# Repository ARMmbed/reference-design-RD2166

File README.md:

# RD2166 Introduction:

The RD2166 Reference Design is a Pelion Ready design based on the Quectel BG96 cellular module and the STM32L475 Microcontroller.

The reference design is a tested and proven starting point targetted towards the creation of both Development Boards and End Products.

# Reference Design Contents:
**Reference Schematic** 
This is the core of reference design, and illustrates where and how the essential components are connected. 

**Reference Application**
Built on mbedOS, and includes Pelion Device Manager. This application has been configured to run on the Reference Design hardware, and will connect to the Pelion Cloud, and is capable of running the cloud based update service.
Please refer to the [\Documentation\RD2166_Readme.md](https://github.com/ARMmbed/reference-design-RD2166/blob/master/Documentation/RD2166_README.md) for instructions on how to build & use this example application.

**Example Implementation** 
Based on the Reference Design, this example implementation is included to demonstrate the Reference Design being used to create real-world hardware. The example implemenation is used within Arm to include the Reference Design into the internal test infrastructure, it is comprised of three parts:

*MCB (Module Carrier Board)* - this has been designed using the Reference Design schematic. In this reference design, the MCB is a standalone STM32L475 MCU.

*MEB (Module Expansion Board)* - this has been designed using the Reference Design schematic. In this reference design, the MEB is a Quectel BG96 module.

*MTB (Module Test Bed)* - this is part of the test infrastructure, and includes DAPLink circuit for programming the device, a range of I/O and loopback paths for automated testing.

# Version Information:
		
| Release | mbed OS | mbed Cloud Client | Release Date | Comment |
| --- | --- | --- | --- | --- | 
|v1.0 | 5.11.5	| 2.0.1.1	| 27/02/2019 | Initial Release
| |  |  |   | 

Back to [Reference Designs](https://github.com/ARMmbed/reference-designs)

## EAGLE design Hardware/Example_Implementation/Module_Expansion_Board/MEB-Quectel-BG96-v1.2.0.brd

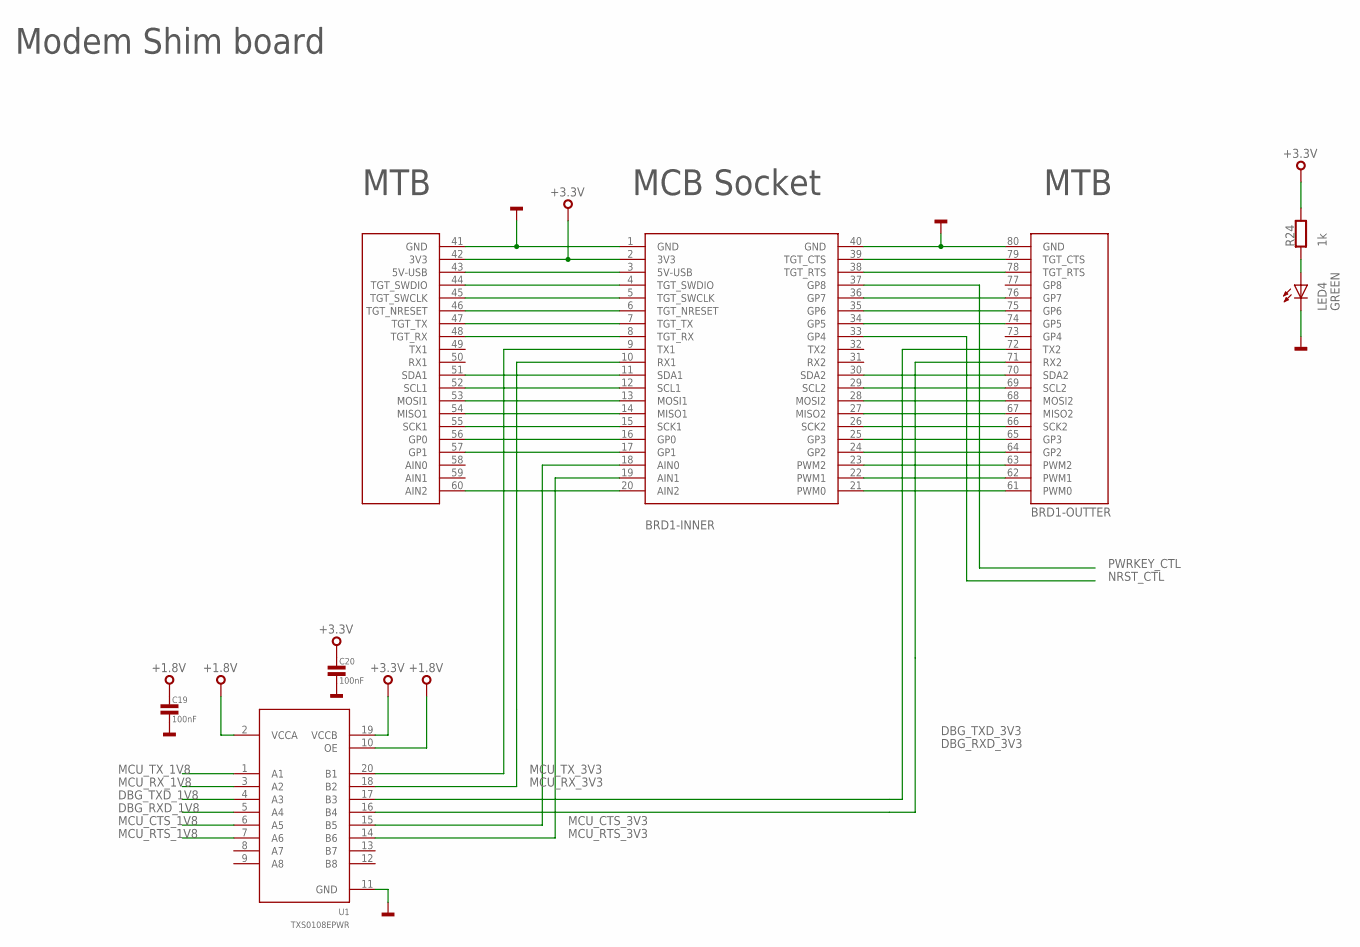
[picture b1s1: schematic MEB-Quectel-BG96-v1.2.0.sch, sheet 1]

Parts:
BRD1: MODULE-SHIM; MODULE_SOCKET
C19, C20: 100nF; 0603
LED4: GREEN; CHIPLED_0603
R24: 1k; 0603
U1: TXS0108EPWR; TSSOP-20

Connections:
+1.8V: C19.1, U1.2 (VCCA), U1.10 (OE); also elsewhere on the board
+3.3V: BRD1.2 (3V3), BRD1.42 (3V3), C20.1, R24.2, U1.19 (VCCB)
DBG_RXD_1V8: U1.5 (A4); also elsewhere on the board
DBG_RXD_3V3: BRD1.71 (RX2), U1.16 (B4)
DBG_TXD_1V8: U1.4 (A3); also elsewhere on the board
DBG_TXD_3V3: BRD1.72 (TX2), U1.17 (B3)
GND: BRD1.1 (GND), BRD1.40 (GND), BRD1.41 (GND), BRD1.80 (GND), C19.2, C20.2, LED4.C, U1.11 (GND); also elsewhere on the board
MCU_CTS_1V8: U1.6 (A5); also elsewhere on the board
MCU_CTS_3V3: BRD1.18 (AIN0), U1.15 (B5)
MCU_RTS_1V8: U1.7 (A6); also elsewhere on the board
MCU_RTS_3V3: BRD1.19 (AIN1), U1.14 (B6)
MCU_RX_1V8: U1.3 (A2); also elsewhere on the board
MCU_RX_3V3: BRD1.10 (RX1), U1.18 (B2)
MCU_TX_1V8: U1.1 (A1); also elsewhere on the board
MCU_TX_3V3: BRD1.9 (TX1), U1.20 (B1)
unnamed: LED4.A, R24.1
unnamed: BRD1.39 (TGT_CTS), BRD1.79 (TGT_CTS)
unnamed: BRD1.38 (TGT_RTS), BRD1.78 (TGT_RTS)
unnamed: BRD1.36 (GP7), BRD1.76 (GP7)
unnamed: BRD1.35 (GP6), BRD1.75 (GP6)
unnamed: BRD1.34 (GP5), BRD1.74 (GP5)
unnamed: BRD1.30 (SDA2), BRD1.70 (SDA2)
unnamed: BRD1.29 (SCL2), BRD1.69 (SCL2)
unnamed: BRD1.28 (MOSI2), BRD1.68 (MOSI2)
unnamed: BRD1.27 (MISO2), BRD1.67 (MISO2)
unnamed: BRD1.26 (SCK2), BRD1.66 (SCK2)
unnamed: BRD1.25 (GP3), BRD1.65 (GP3)
unnamed: BRD1.24 (GP2), BRD1.64 (GP2)
unnamed: BRD1.23 (PWM2), BRD1.63 (PWM2)
unnamed: BRD1.22 (PWM1), BRD1.62 (PWM1)
unnamed: BRD1.21 (PWM0), BRD1.61 (PWM0)
unnamed: BRD1.3 (5V-USB), BRD1.43 (5V-USB)
unnamed: BRD1.4 (TGT_SWDIO), BRD1.44 (TGT_SWDIO)
unnamed: BRD1.5 (TGT_SWCLK), BRD1.45 (TGT_SWCLK)
unnamed: BRD1.6 (TGT_NRESET), BRD1.46 (TGT_NRESET)
unnamed: BRD1.7 (TGT_TX), BRD1.47 (TGT_TX)
unnamed: BRD1.8 (TGT_RX), BRD1.48 (TGT_RX)
unnamed: BRD1.11 (SDA1), BRD1.51 (SDA1)
unnamed: BRD1.12 (SCL1), BRD1.52 (SCL1)
unnamed: BRD1.13 (MOSI1), BRD1.53 (MOSI1)
unnamed: BRD1.14 (MISO1), BRD1.54 (MISO1)
unnamed: BRD1.15 (SCK1), BRD1.55 (SCK1)
unnamed: BRD1.16 (GP0), BRD1.56 (GP0)
unnamed: BRD1.17 (GP1), BRD1.57 (GP1)
unnamed: BRD1.20 (AIN2), BRD1.60 (AIN2)
NRST_CTL: BRD1.33 (GP4); also elsewhere on the board
PWRKEY_CTL: BRD1.37 (GP8); also elsewhere on the board

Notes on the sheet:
Modem Shim board
MCB Socket
MTB

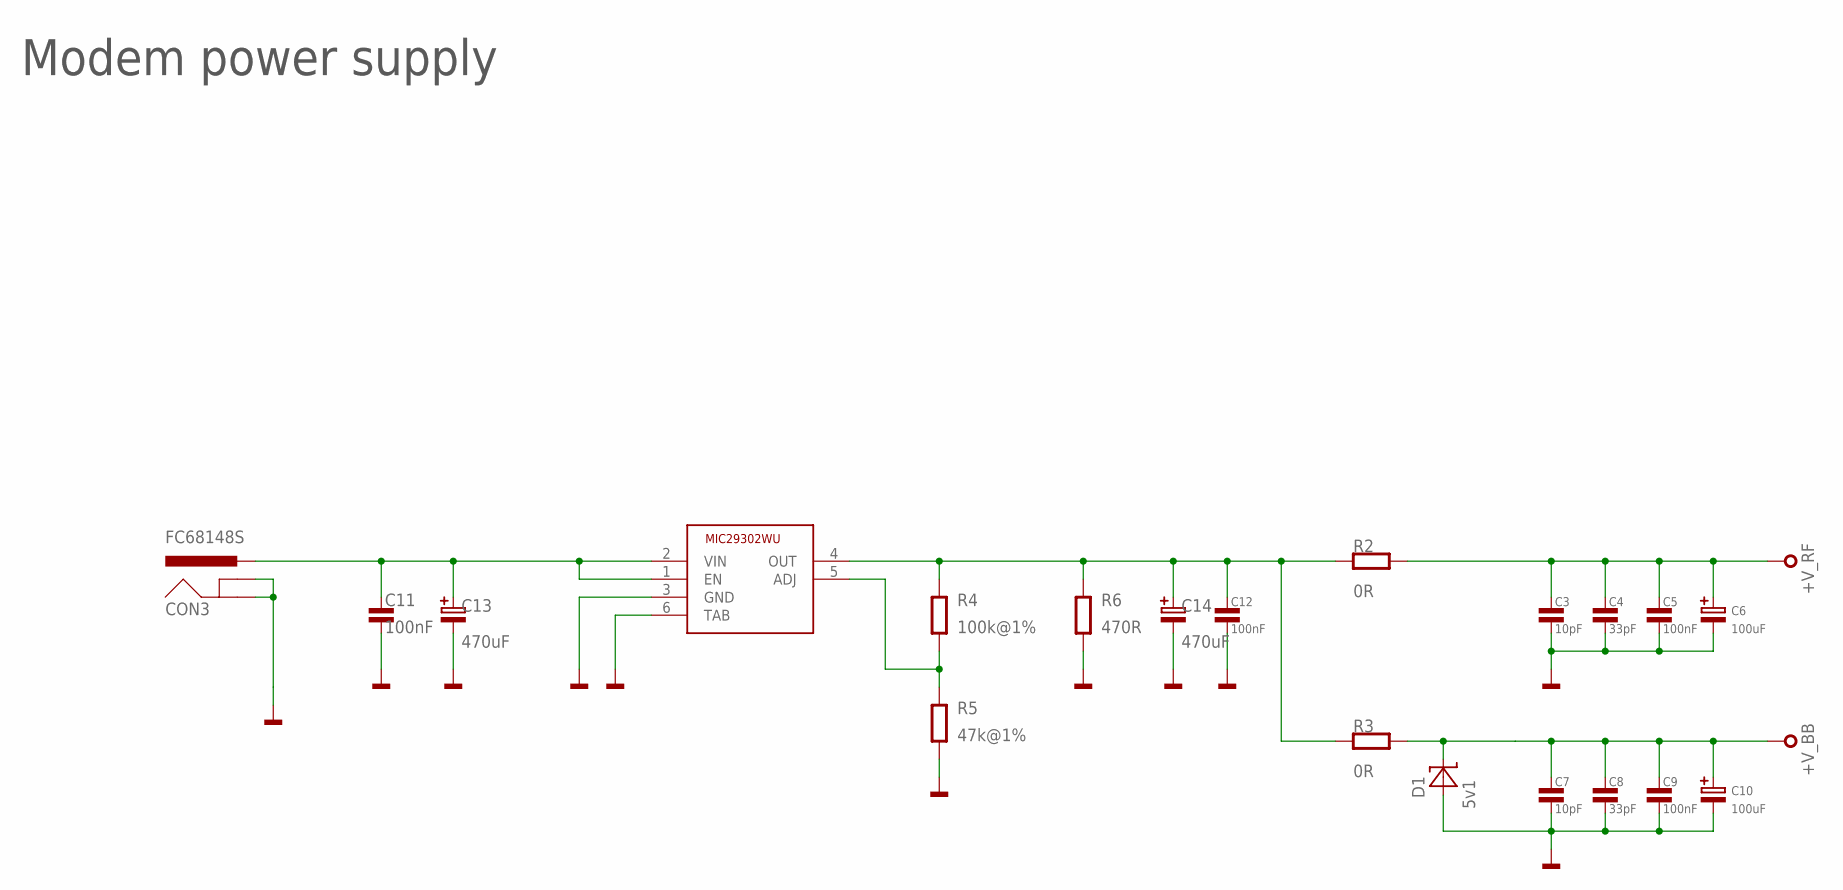
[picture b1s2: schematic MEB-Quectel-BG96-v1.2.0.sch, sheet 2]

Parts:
C3, C7: 10pF; 0603
C4, C8: 33pF; 0603
C5, C9, C11, C12: 100nF; 0603
C6, C10: 100uF; SMC_A
C13, C14: 470uF; PANASONIC_F
CON3: FC68148S
D1: 5v1; SOD123
IC1: MIC29302WU; TO263-5
R2, R3: 0R; 0603
R4: 100k@1%; 0603
R5: 47k@1%; 0603
R6: 470R; 0603

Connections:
+V_BB: C7.1, C8.1, C9.1, C10.+, D1.2 (C), R3.2; also elsewhere on the board
+V_RF: C3.1, C4.1, C5.1, C6.+, R2.2; also elsewhere on the board
GND: C3.2, C4.2, C5.2, C6.-, C7.2, C8.2, C9.2, C10.-, C11.2, C12.2, C13.-, C14.-, CON3.2 (GNDBREAK), CON3.3 (GND), D1.1 (A), IC1.3 (GND), IC1.6 (TAB), R5.1, R6.1; also elsewhere on the board
unnamed: C11.1, C13.+, CON3.1-1 (PWR), CON3.1-2 (PWR), IC1.1 (EN), IC1.2 (VIN)
unnamed: IC1.5 (ADJ), R4.1, R5.2
unnamed: C12.1, C14.+, IC1.4 (OUT), R2.1, R3.1, R4.2, R6.2

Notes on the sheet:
Modem power supply

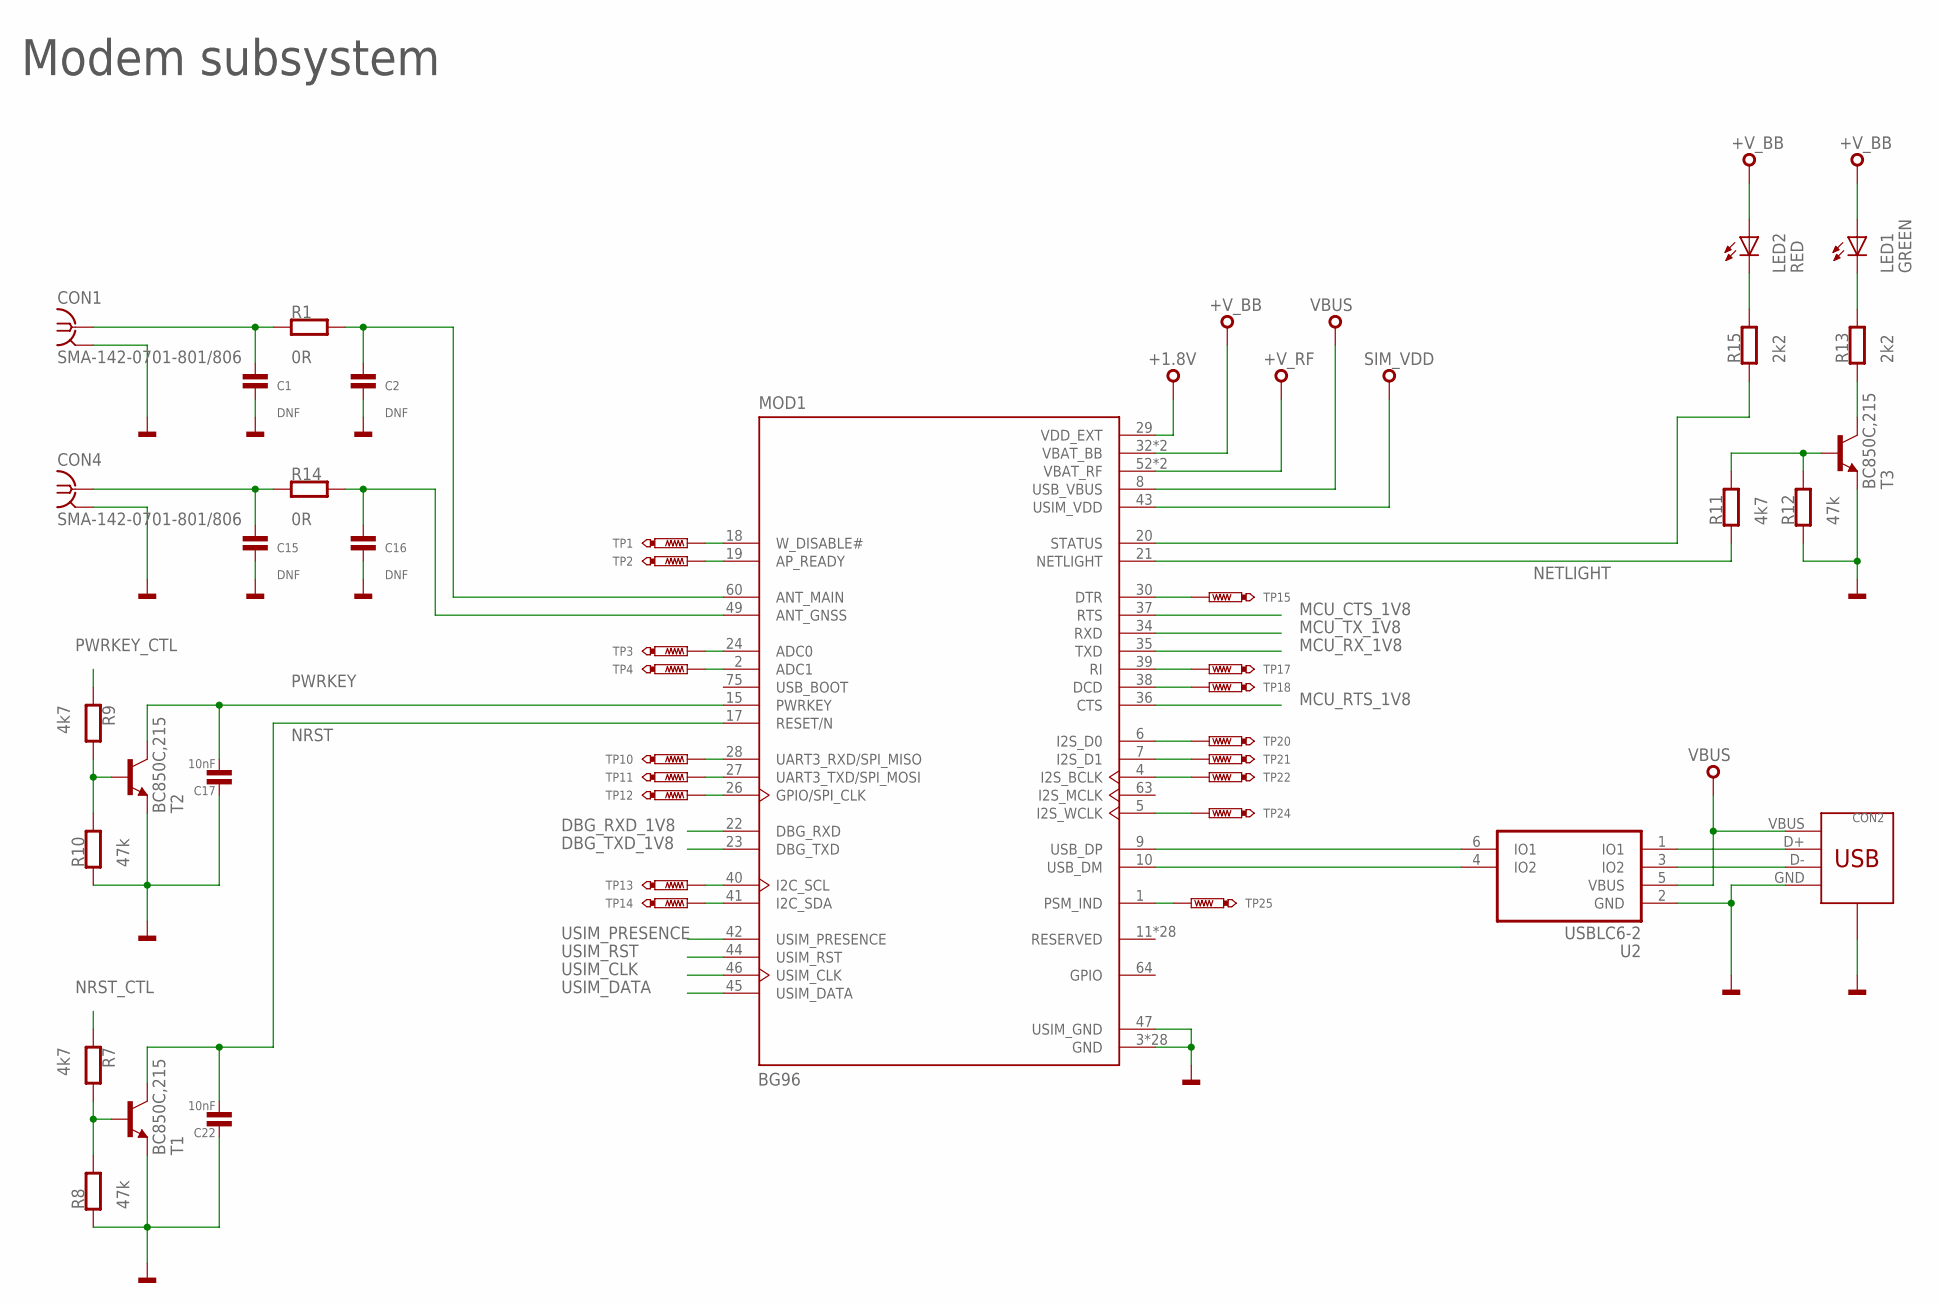
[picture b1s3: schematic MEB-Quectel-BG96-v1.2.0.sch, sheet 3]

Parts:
C1, C2, C15, C16: DNF; 0603
C17, C22: 10nF; 0603
CON1, CON4: SMA-142-0701-801/806; J502-ND-142-0701-801/806
CON2: 47346-0001; USB-MICRO-B-H
LED1: GREEN; CHIPLED_0603
LED2: RED; CHIPLED_0603
MOD1: BG96; LTE_MODULE_BG96
R1, R14: 0R; 0603
R7, R9, R11: 4k7; 0603
R8, R10, R12: 47k; 0603
R13, R15: 2k2; 0603
T1, T2, T3: BC850C,215; SOT23-3
TP1, TP2, TP3, TP4, TP10, TP11, TP12, TP13, TP14, TP15, TP17, TP18, TP20, TP21, TP22, TP24, TP25: TEST_POINT-50R-SMD; TP50-SMD
U2: USBLC6-2SC6; SOT23-6L

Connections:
+1.8V: MOD1.29 (VDD_EXT); also elsewhere on the board
+V_BB: LED1.A, LED2.A, MOD1.32 (VBAT_BB), MOD1.33 (VBAT_BB); also elsewhere on the board
+V_RF: MOD1.52 (VBAT_RF), MOD1.53 (VBAT_RF); also elsewhere on the board
DBG_RXD_1V8: MOD1.22 (DBG_RXD); also elsewhere on the board
DBG_TXD_1V8: MOD1.23 (DBG_TXD); also elsewhere on the board
GND: C1.1, C2.1, C15.1, C16.1, C17.1, C22.1, CON1.G@1 (2), CON1.G@2 (2), CON1.G@3 (2), CON1.G@4 (2), CON2.GND, CON2.GND1 (SHEILD), CON2.GND2 (SHEILD), CON2.GND3 (SHEILD), CON2.GND4 (SHEILD), CON4.G@1 (2), CON4.G@2 (2), CON4.G@3 (2), CON4.G@4 (2), MOD1.3 (GND), MOD1.31 (GND), MOD1.47 (USIM_GND), MOD1.48 (GND), MOD1.50 (GND), MOD1.54 (GND), MOD1.55 (GND), MOD1.58 (GND), MOD1.59 (GND), MOD1.61 (GND), MOD1.62 (GND), MOD1.67 (GND), MOD1.68 (GND), MOD1.69 (GND), MOD1.70 (GND), MOD1.71 (GND), MOD1.72 (GND), MOD1.73 (GND), MOD1.74 (GND), MOD1.79 (GND), MOD1.80 (GND), MOD1.81 (GND), MOD1.82 (GND), MOD1.89 (GND), MOD1.90 (GND), MOD1.91 (GND), MOD1.100 (GND), MOD1.101 (GND), MOD1.102 (GND), R8.1, R10.1, R12.1, T1.2 (E), T2.2 (E), T3.2 (E), U2.2 (GND); also elsewhere on the board
MCU_CTS_1V8: MOD1.37 (RTS); also elsewhere on the board
MCU_RTS_1V8: MOD1.36 (CTS); also elsewhere on the board
MCU_RX_1V8: MOD1.35 (TXD); also elsewhere on the board
MCU_TX_1V8: MOD1.34 (RXD); also elsewhere on the board
unnamed: LED2.C, R15.2
unnamed: LED1.C, R13.2
unnamed: MOD1.30 (DTR), TP15.TP
unnamed: MOD1.39 (RI), TP17.TP
unnamed: MOD1.38 (DCD), TP18.TP
unnamed: C1.2, CON1.1, R1.1
unnamed: C2.2, MOD1.60 (ANT_MAIN), R1.2
unnamed: C15.2, CON4.1, R14.1
unnamed: C16.2, MOD1.49 (ANT_GNSS), R14.2
unnamed: R9.2, R10.2, T2.1 (B)
unnamed: R7.2, R8.2, T1.1 (B)
unnamed: MOD1.6 (I2S_D0), TP20.TP
unnamed: CON2.D+, U2.1 (IO1)
unnamed: MOD1.7 (I2S_D1), TP21.TP
unnamed: MOD1.4 (I2S_BCLK), TP22.TP
unnamed: CON2.D-, U2.3 (IO2)
unnamed: MOD1.9 (USB_DP), U2.6 (IO1)
unnamed: MOD1.10 (USB_DM), U2.4 (IO2)
unnamed: R11.2, R12.2, T3.1 (B)
unnamed: MOD1.5 (I2S_WCLK), TP24.TP
unnamed: MOD1.1 (PSM_IND), TP25.TP
unnamed: MOD1.41 (I2C_SDA), TP14.TP
unnamed: MOD1.40 (I2C_SCL), TP13.TP
unnamed: MOD1.26 (GPIO/SPI_CLK), TP12.TP
unnamed: MOD1.27 (UART3_TXD/SPI_MOSI), TP11.TP
unnamed: MOD1.28 (UART3_RXD/SPI_MISO), TP10.TP
unnamed: MOD1.18 (W_DISABLE#), TP1.TP
unnamed: MOD1.19 (AP_READY), TP2.TP
unnamed: MOD1.2 (ADC1), TP4.TP
unnamed: MOD1.24 (ADC0), TP3.TP
NETLIGHT: MOD1.21 (NETLIGHT), R11.1
NRST: C22.2, MOD1.17 (RESET/N), T1.3 (C)
NRST1: R13.1, T3.3 (C)
NRST_CTL: R7.1; also elsewhere on the board
PWRKEY: C17.2, MOD1.15 (PWRKEY), T2.3 (C)
PWRKEY_CTL: R9.1; also elsewhere on the board
SIM_VDD: MOD1.43 (USIM_VDD); also elsewhere on the board
STATUS: MOD1.20 (STATUS), R15.1
USIM_CLK: MOD1.46 (USIM_CLK); also elsewhere on the board
USIM_DATA: MOD1.45 (USIM_DATA); also elsewhere on the board
USIM_PRESENCE: MOD1.42 (USIM_PRESENCE); also elsewhere on the board
USIM_RST: MOD1.44 (USIM_RST); also elsewhere on the board
VBUS: CON2.VBUS, MOD1.8 (USB_VBUS), U2.5 (VBUS)

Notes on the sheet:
Modem subsystem

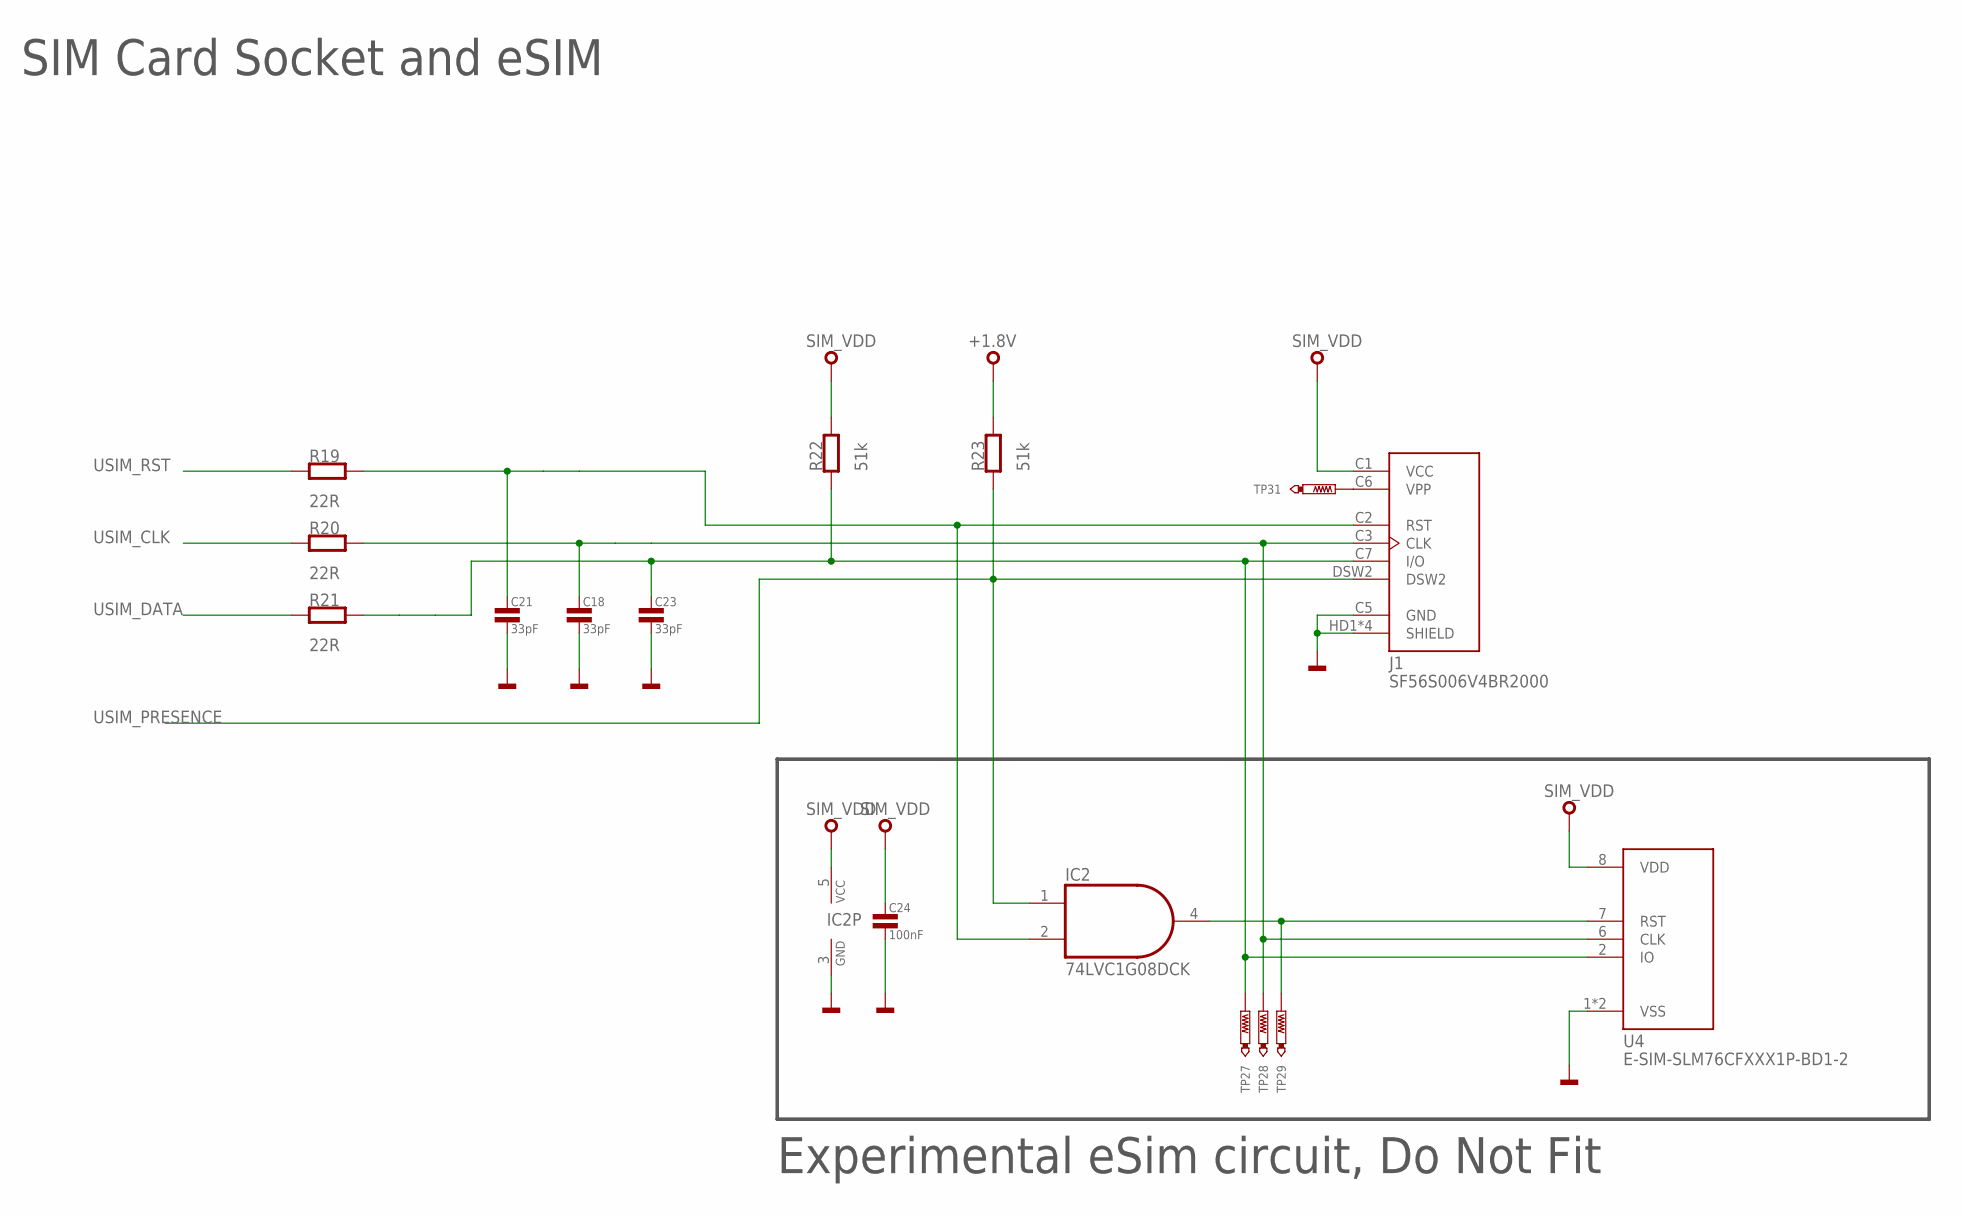
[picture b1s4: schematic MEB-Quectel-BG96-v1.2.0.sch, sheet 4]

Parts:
C18, C21, C23: 33pF; 0603
C24: 100nF; 0603
IC2: 74LVC1G08DCK; SC70-5
J1: SF56S006V4BR2000; JAE_SF56S006V4BR2000
R19, R20, R21: 22R; 0603
R22, R23: 51k; 0603
TP27, TP28, TP29, TP31: TEST_POINT-50R-SMD; TP50-SMD
U4: E-SIM-SLM76CFXXX1P-BD1-2; VQFN-8-1

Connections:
+1.8V: R23.2; also elsewhere on the board
GND: C18.2, C21.2, C23.2, C24.2, IC2.3 (GND), J1.C5 (GND), J1.HD1 (SHIELD), J1.HD2,DSW1 (SHIELD), J1.HD3 (SHIELD), J1.HD4 (SHIELD), U4.1 (VSS), U4.P (VSS); also elsewhere on the board
unnamed: IC2.4 (O), TP29.TP, U4.7 (RST)
unnamed: C21.1, IC2.2 (I1), J1.C2 (RST), R19.2
unnamed: C18.1, J1.C3 (CLK), R20.2, TP28.TP, U4.6 (CLK)
unnamed: C23.1, J1.C7 (I/O), R21.2, R22.1, TP27.TP, U4.2 (IO)
unnamed: J1.C6 (VPP), TP31.TP
SIM_VDD: C24.1, IC2.5 (VCC), J1.C1 (VCC), R22.2, U4.8 (VDD); also elsewhere on the board
USIM_CLK: R20.1; also elsewhere on the board
USIM_DATA: R21.1; also elsewhere on the board
USIM_PRESENCE: IC2.1 (I0), J1.DSW2, R23.1; also elsewhere on the board
USIM_RST: R19.1; also elsewhere on the board

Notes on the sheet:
SIM Card Socket and eSIM
Experimental eSim circuit, Do Not Fit

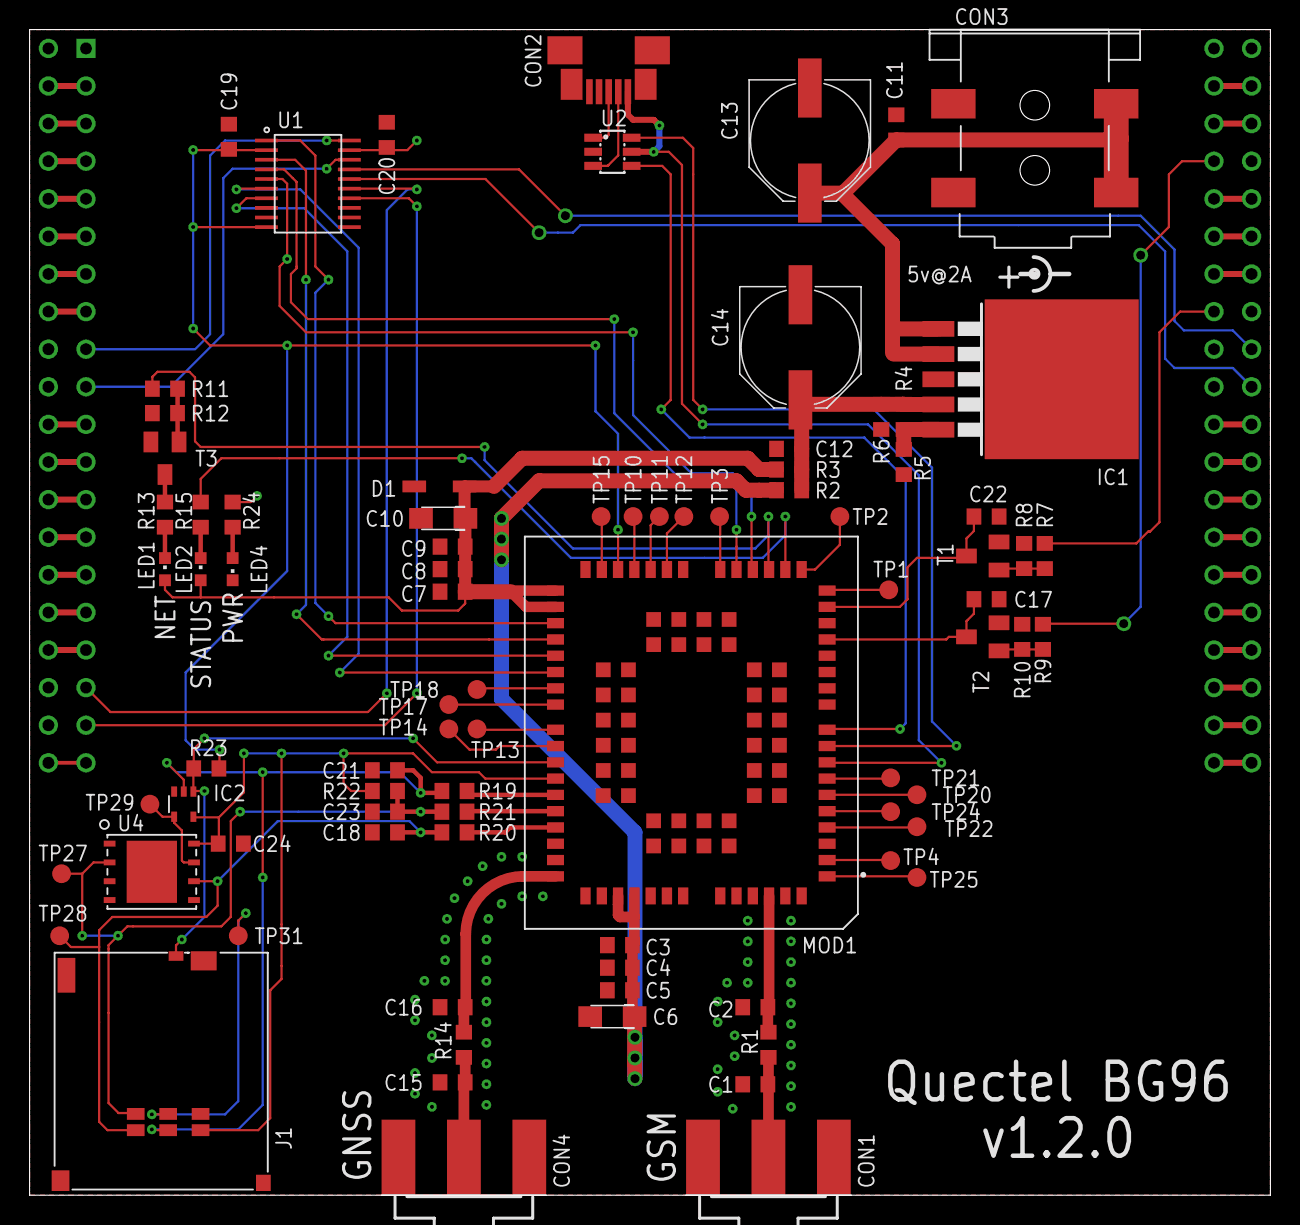
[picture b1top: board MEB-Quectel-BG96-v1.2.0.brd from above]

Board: 2 copper layers, 83.8 x 78.7 mm, 85 parts (0 on the bottom side), 98 nets.

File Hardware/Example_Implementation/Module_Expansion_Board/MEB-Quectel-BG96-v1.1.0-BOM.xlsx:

Qty | Value | Device | Package | Parts | Description | MF | MFN | OC-DIGIKEY | OC-MOUSER | OC_FARNELL | OC_NEWARK
4 | 0R | R0603 | 0603 | R1, R2, R3, R14 | Resistor |  |  | 311-0.0GRCT-ND | 603-RC0603JR-070RL
1 | 100k@1% | R0603 | 0603 | R4 | Resistor |  |  | 311-100KGRCT-ND | 603-RC0603JR-07100KL
7 | 100nF | C0603 | 0603 | C5, C9, C11, C12, C19, C20, C24 | Capacitor |  |  | 732-7989-1-ND | 710-885012206071 | 2392304
2 | 100uF | C-POLA | SMC_A | C6, C10 | Polarised capacitor |  |  | 478-8152-1-ND | 74-TMCMA0J107MTRF | 2429372
2 | 10nF | C0603 | 0603 | C17, C22 | Capacitor |  |  | 445-5100-2-ND | 710-885012206065 | 2525109
2 | 10pF | C0603 | 0603 | C3, C7 | Capacitor |  |  | 732-7793-1-ND | 710-885012006051 | 2495133
1 | 1k | R0603 | 0603 | R24 | Resistor |  |  | 311-1.0KGRCT-ND | 603-RC0603JR-071KL | 2447272
3 | 22R | R0603 | 0603 | R19, R20, R21 | Resistor |  |  | P22.0HCT-ND | 667-ERJ-1GNF22R0C | 2302291
2 | 2k2 | R0603 | 0603 | R13, R15 | Resistor |  |  | 311-2.2KGRCT-ND | 603-RC0603JR-072K2L
5 | 33pF | C0603 | 0603 | C4, C8, C18, C21, C23 | Capacitor |  |  | 311-1468-1-ND | CC0603JRNPO0BN330 | 2524942
1 | 470R | R0603 | 0603 | R6 | Resistor |  |  | 311-470GRCT-ND | 603-RC0603JR-07470RL
2 | 470uF | CPOL-EU150CLZ-0810 | 150CLZ-0810 | C13, C14 | POLARIZED CAPACITOR, European symbol |  |  | WM17141CT-ND | 538-47346-0001 | 1568026
1 | 47346-0001 | 47346-0001 | USB-MICRO-B-H | CON2 | USB Receptacle Horizontal Micro Type B | MOLEX | 47346-0001 | WM17141CT-ND | 538-47346-0001 | 1568026 | 1568026
4 | 47k@1% | R0603 | 0603 | R5, R8, R10, R12 | Resistor |  |  | 311-47kGRCT-ND | 603-RC0603JR-0747KL
3 | 4k7 | R0603 | 0603 | R7, R9, R11 | Resistor |  |  | 311-4.7kGRCT-ND | 603-RC0603JR-074K7L | 2446702
2 | 51k | R0603 | 0603 | R22, R23 | Resistor |  |  | 311-51KNCT-ND | 603-RC0201JR-0751KL | 2059471
1 | 5v1 | DIODE-ZENER | SOD123 | D1 |  |  |  | BZT52C5V1-E3-08CT-ND | 78-BZT52C5V1-E3-08 | 2690025
1 | 74AHC1G08DCK | 74AHC1G08DCK | SC70-5 | IC2 | 2-input AND gate |  |  | 296-11604-1-ND | 595-SN74LVC1G125DCKR | 1470768
3 | BC850C,215 | BC850C,215 | SOT23-3 | T1, T2, T3 | BJT NPN | NXP Semiconductors | BC850C,215 | 568-6077-1-ND | 771-BC850C-T/R |  | 75R0745
1 | BG96 | BG96 | LTE_MODULE_BG96 | MOD1 | Lte Cat.M1 Module For Global Sku | Quectel
4 | DNF | C0603 | 0603 | C1, C2, C15, C16 | Capacitor
1 | FC68148S | FC68148S | FC68148S | CON3 | Power Jack | Cliff | FC68148S |  |  | 1889309
2 | GREEN | LED0603 | CHIPLED_0603 | LED1, LED4 | LED SMD |  |  | 732-4971-1-ND | 710-150060GS75000 | 2322070
1 | MIC29302WU | MIC29302WU | TO263-5 | IC1 |  | Microchip |  | 576-1125-1-ND | 998-MIC29302WUTR | 2510027
1 | RED | LED0603 | CHIPLED_0603 | LED2 | LED SMD |  |  | 732-4978-1-ND | 710-150060RS75000 | 2322071
1 | SF56S006V4BR2000 | SF56S006V4BR2000 | JAE_SF56S006V4BR2000 | J1 | CONN MICRO SIM CARD PUSH-PUSH | JAE Electronics |  | 670-2834-1-ND
2 | SMA-142-0701-801/806 | SMA-142-0701-801/806 | J502-ND-142-0701-801/806 | CON1, CON4 | SMA 50 Ohm End Launch Jack Receptacle | JOHNSON COMPONENTS |  | J502-ND | 530-142-0701-801 | 1608592 | 90F2624
1 | TXS0108EPWR | TXS0108EPWR | TSSOP-20 | U1 | 8-Bit Bi-directional, Level-Shifting | Texas Instruments | TXS0108EPWR | 296-23011-1-ND | 595-TXS0108EPWR | 1702548 | 05R8300
1 | USBLC6-2SC6 | USBLC6-2SC6 | SOT23-6L | U2 | 2 line Transient voltage suppressor | STMicro | USBLC6-2SC6Y | 497-5235-1-ND | 511-USBLC6-2SC6 | 1269406 | 2629711

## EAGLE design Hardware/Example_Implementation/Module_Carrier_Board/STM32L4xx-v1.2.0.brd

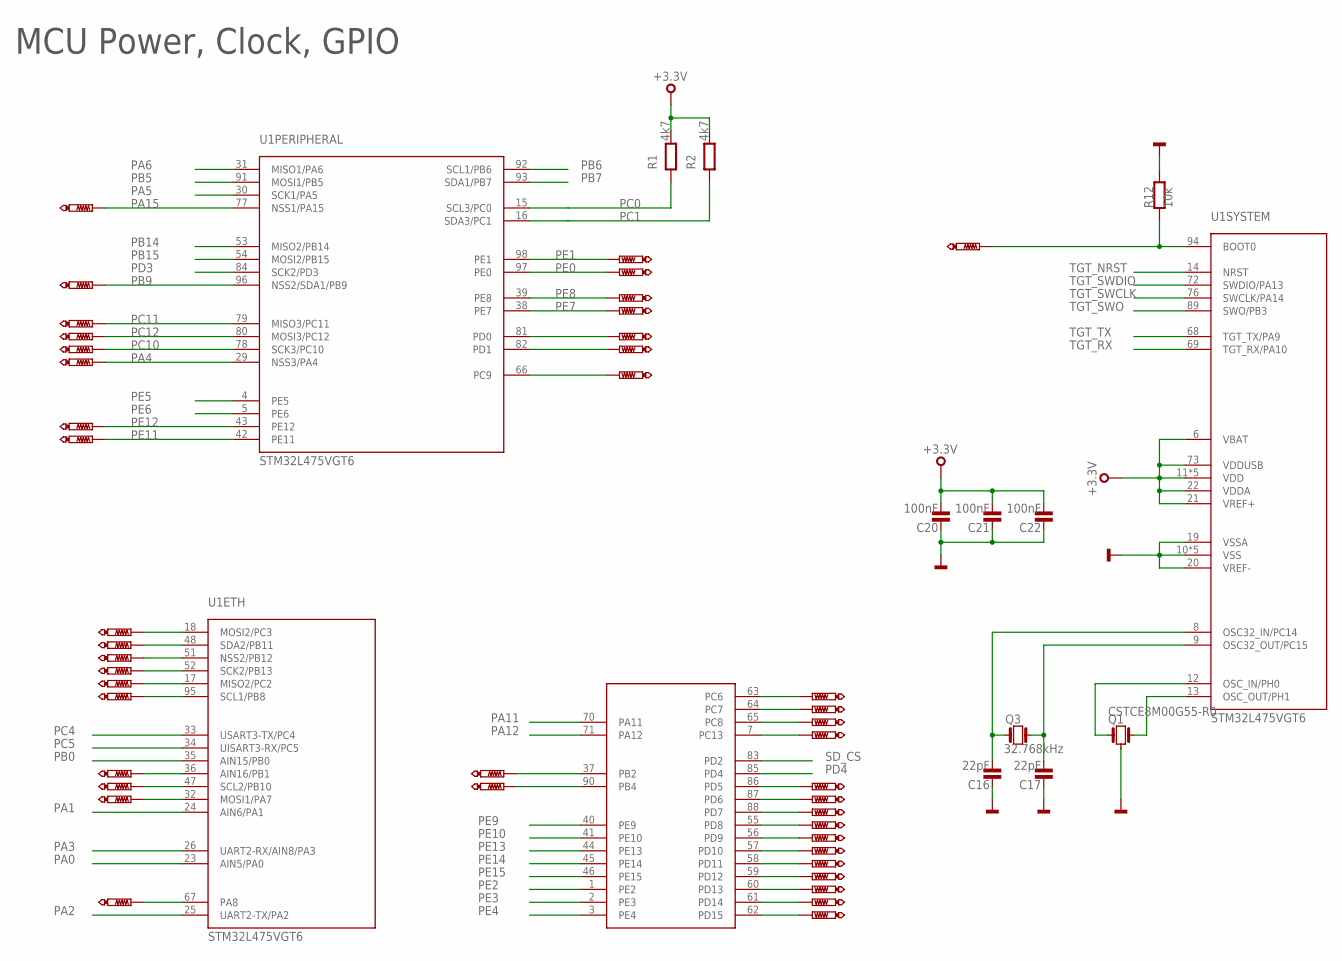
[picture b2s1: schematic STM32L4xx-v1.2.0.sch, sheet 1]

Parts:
C16, C17: 22pF; 0603
C20, C21, C22: 100nF; 0402
Q1: CSTCE8M00G55-R0
Q3: 32.768kHz; FC135
R1, R2: 4k7; 0402
R12: 10k; 0402
TP3, TP4, TP5, TP6, TP7, TP8, TP9, TP10, TP11, TP12, TP13, TP14, TP15, TP16, TP17, TP18, TP19, TP20, TP21, TP22, TP23, TP24, TP25, TP26, TP27, TP28, TP29, TP30, TP31, TP32, TP33, TP34, TP35, TP36, TP37, TP38, TP39, TP40, TP41, TP42, TP43, TP44, TP45: PTR1TP06R; TP06R
U1: STM32L475VGT6; QFP50P1600X1600X160-100N

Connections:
+3.3V: C20.2, C21.2, C22.2, R1.2, R2.2, U1.6 (VBAT), U1.11 (VDD), U1.21 (VREF+), U1.22 (VDDA), U1.28 (VDD), U1.50 (VDD), U1.73 (VDDUSB), U1.75 (VDD), U1.100 (VDD); also elsewhere on the board
GND: C16.1, C17.1, C20.1, C21.1, C22.1, Q1.2, R12.2, U1.10 (VSS), U1.19 (VSSA), U1.20 (VREF-), U1.27 (VSS), U1.49 (VSS), U1.74 (VSS), U1.99 (VSS); also elsewhere on the board
unnamed: TP5.TP, U1.55 (PD8)
unnamed: TP21.TP, U1.62 (PD15)
unnamed: R12.1, TP6.TP, U1.94 (BOOT0)
unnamed: TP26.TP, U1.37 (PB2)
unnamed: TP25.TP, U1.7 (PC13)
unnamed: TP27.TP, U1.18 (MOSI2/PC3)
unnamed: TP28.TP, U1.48 (SDA2/PB11)
unnamed: TP3.TP, U1.81 (PD0)
unnamed: TP29.TP, U1.51 (NSS2/PB12)
unnamed: TP30.TP, U1.52 (SCK2/PB13)
unnamed: Q1.1, U1.12 (OSC_IN/PH0)
unnamed: Q1.3, U1.13 (OSC_OUT/PH1)
unnamed: C17.2, Q3.X2 (2), U1.9 (OSC32_OUT/PC15)
unnamed: TP31.TP, U1.17 (MISO2/PC2)
unnamed: C16.2, Q3.X1 (1), U1.8 (OSC32_IN/PC14)
unnamed: TP4.TP, U1.82 (PD1)
unnamed: TP7.TP, U1.66 (PC9)
unnamed: TP32.TP, U1.95 (SCL1/PB8)
unnamed: TP33.TP, U1.67 (PA8)
unnamed: TP18.TP, U1.88 (PD7)
unnamed: TP11.TP, U1.90 (PB4)
unnamed: TP34.TP, U1.36 (AIN16/PB1)
unnamed: TP20.TP, U1.86 (PD5)
unnamed: TP19.TP, U1.87 (PD6)
unnamed: TP17.TP, U1.65 (PC8)
unnamed: TP16.TP, U1.64 (PC7)
unnamed: TP36.TP, U1.47 (SCL2/PB10)
unnamed: TP15.TP, U1.63 (PC6)
unnamed: TP12.TP, U1.60 (PD13)
unnamed: TP35.TP, U1.32 (MOSI1/PA7)
unnamed: TP13.TP, U1.56 (PD9)
unnamed: TP10.TP, U1.57 (PD10)
unnamed: TP22.TP, U1.58 (PD11)
unnamed: TP23.TP, U1.59 (PD12)
unnamed: TP24.TP, U1.61 (PD14)
PA0: U1.23 (AIN5/PA0); also elsewhere on the board
PA1: U1.24 (AIN6/PA1); also elsewhere on the board
PA2: U1.25 (UART2-TX/PA2); also elsewhere on the board
PA3: U1.26 (UART2-RX/AIN8/PA3); also elsewhere on the board
PA4: TP44.TP, U1.29 (NSS3/PA4)
PA5: U1.30 (SCK1/PA5); also elsewhere on the board
PA6: U1.31 (MISO1/PA6); also elsewhere on the board
PA11: U1.70 (PA11); also elsewhere on the board
PA12: U1.71 (PA12); also elsewhere on the board
PA15: TP37.TP, U1.77 (NSS1/PA15)
PB0: U1.35 (AIN15/PB0); also elsewhere on the board
PB5: U1.91 (MOSI1/PB5); also elsewhere on the board
PB6: U1.92 (SCL1/PB6); also elsewhere on the board
PB7: U1.93 (SDA1/PB7); also elsewhere on the board
PB9: TP14.TP, U1.96 (NSS2/SDA1/PB9)
PB14: U1.53 (MISO2/PB14); also elsewhere on the board
PB15: U1.54 (MOSI2/PB15); also elsewhere on the board
PC0: R1.1, U1.15 (SCL3/PC0); also elsewhere on the board
PC1: R2.1, U1.16 (SDA3/PC1); also elsewhere on the board
PC4: U1.33 (USART3-TX/PC4); also elsewhere on the board
PC5: U1.34 (UISART3-RX/PC5); also elsewhere on the board
PC10: TP43.TP, U1.78 (SCK3/PC10); also elsewhere on the board
PC11: TP41.TP, U1.79 (MISO3/PC11)
PC12: TP42.TP, U1.80 (MOSI3/PC12)
PD3: U1.84 (SCK2/PD3); also elsewhere on the board
PD4: U1.85 (PD4); also elsewhere on the board
PE0: TP39.TP, U1.97 (PE0)
PE1: TP38.TP, U1.98 (PE1)
PE2: U1.1 (PE2); also elsewhere on the board
PE3: U1.2 (PE3); also elsewhere on the board
PE4: U1.3 (PE4); also elsewhere on the board
PE5: U1.4 (PE5); also elsewhere on the board
PE6: U1.5 (PE6); also elsewhere on the board
PE7: TP45.TP, U1.38 (PE7)
PE8: TP40.TP, U1.39 (PE8)
PE9: U1.40 (PE9); also elsewhere on the board
PE10: U1.41 (PE10); also elsewhere on the board
PE11: TP8.TP, U1.42 (PE11)
PE12: TP9.TP, U1.43 (PE12)
PE13: U1.44 (PE13); also elsewhere on the board
PE14: U1.45 (PE14); also elsewhere on the board
PE15: U1.46 (PE15); also elsewhere on the board
SD_CS: U1.83 (PD2); also elsewhere on the board
TGT_NRST: U1.14 (NRST); also elsewhere on the board
TGT_RX: U1.69 (TGT_RX/PA10); also elsewhere on the board
TGT_SWCLK: U1.76 (SWCLK/PA14); also elsewhere on the board
TGT_SWDIO: U1.72 (SWDIO/PA13); also elsewhere on the board
TGT_SWO: U1.89 (SWO/PB3); also elsewhere on the board
TGT_TX: U1.68 (TGT_TX/PA9); also elsewhere on the board

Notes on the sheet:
MCU Power, Clock, GPIO
